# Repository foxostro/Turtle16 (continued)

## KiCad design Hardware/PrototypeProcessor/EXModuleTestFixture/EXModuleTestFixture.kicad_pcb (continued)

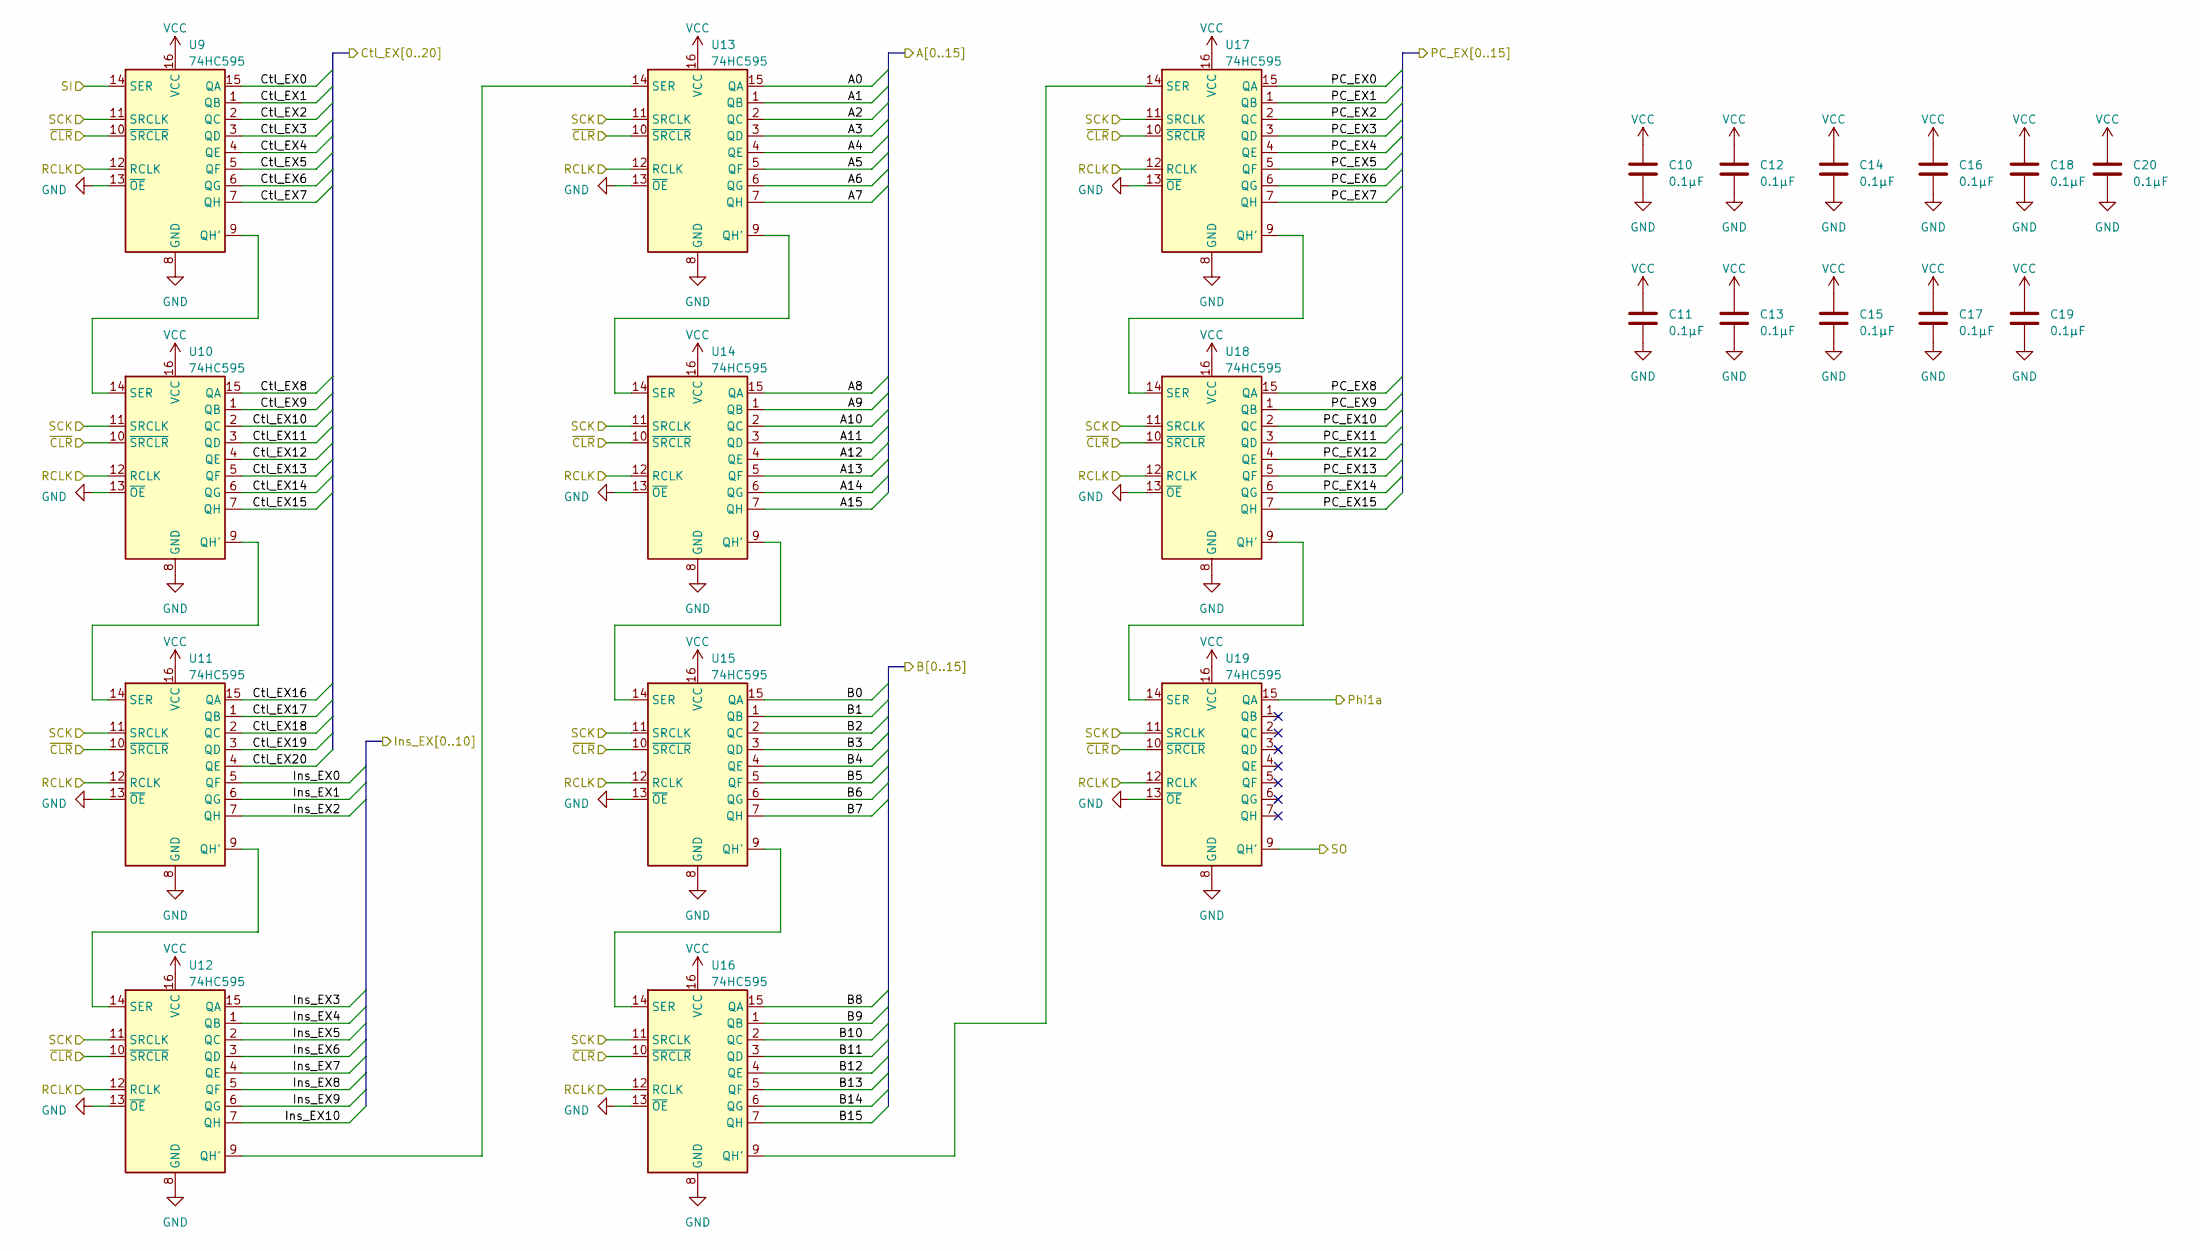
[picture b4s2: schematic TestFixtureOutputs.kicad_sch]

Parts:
C10, C11, C12, C13, C14, C15, C16, C17, C18, C19, C20: 0.1µF; C_0603_1608Metric
U9, U10, U11, U12, U13, U14, U15, U16, U17, U18, U19: 74HC595; TSSOP-16_4.4x5mm_P0.65mm

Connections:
/EX Prototype Inputs/A0: U13.15 (QA); also elsewhere on the board
/EX Prototype Inputs/A1: U13.1 (QB); also elsewhere on the board
/EX Prototype Inputs/A2: U13.2 (QC); also elsewhere on the board
/EX Prototype Inputs/A3: U13.3 (QD); also elsewhere on the board
/EX Prototype Inputs/A4: U13.4 (QE); also elsewhere on the board
/EX Prototype Inputs/A5: U13.5 (QF); also elsewhere on the board
/EX Prototype Inputs/A6: U13.6 (QG); also elsewhere on the board
/EX Prototype Inputs/A7: U13.7 (QH); also elsewhere on the board
/EX Prototype Inputs/A8: U14.15 (QA); also elsewhere on the board
/EX Prototype Inputs/A9: U14.1 (QB); also elsewhere on the board
/EX Prototype Inputs/A10: U14.2 (QC); also elsewhere on the board
/EX Prototype Inputs/A11: U14.3 (QD); also elsewhere on the board
/EX Prototype Inputs/A12: U14.4 (QE); also elsewhere on the board
/EX Prototype Inputs/A13: U14.5 (QF); also elsewhere on the board
/EX Prototype Inputs/A14: U14.6 (QG); also elsewhere on the board
/EX Prototype Inputs/A15: U14.7 (QH); also elsewhere on the board
/EX Prototype Inputs/B0: U15.15 (QA); also elsewhere on the board
/EX Prototype Inputs/B1: U15.1 (QB); also elsewhere on the board
/EX Prototype Inputs/B2: U15.2 (QC); also elsewhere on the board
/EX Prototype Inputs/B3: U15.3 (QD); also elsewhere on the board
/EX Prototype Inputs/B4: U15.4 (QE); also elsewhere on the board
/EX Prototype Inputs/B5: U15.5 (QF); also elsewhere on the board
/EX Prototype Inputs/B6: U15.6 (QG); also elsewhere on the board
/EX Prototype Inputs/B7: U15.7 (QH); also elsewhere on the board
/EX Prototype Inputs/B8: U16.15 (QA); also elsewhere on the board
/EX Prototype Inputs/B9: U16.1 (QB); also elsewhere on the board
/EX Prototype Inputs/B10: U16.2 (QC); also elsewhere on the board
/EX Prototype Inputs/B11: U16.3 (QD); also elsewhere on the board
/EX Prototype Inputs/B12: U16.4 (QE); also elsewhere on the board
/EX Prototype Inputs/B13: U16.5 (QF); also elsewhere on the board
/EX Prototype Inputs/B14: U16.6 (QG); also elsewhere on the board
/EX Prototype Inputs/B15: U16.7 (QH); also elsewhere on the board
/EX Prototype Inputs/Ctl_EX0: U9.15 (QA); also elsewhere on the board
/EX Prototype Inputs/Ctl_EX1: U9.1 (QB); also elsewhere on the board
/EX Prototype Inputs/Ctl_EX2: U9.2 (QC); also elsewhere on the board
/EX Prototype Inputs/Ctl_EX3: U9.3 (QD); also elsewhere on the board
/EX Prototype Inputs/Ctl_EX4: U9.4 (QE); also elsewhere on the board
/EX Prototype Inputs/Ctl_EX5: U9.5 (QF); also elsewhere on the board
/EX Prototype Inputs/Ctl_EX6: U9.6 (QG); also elsewhere on the board
/EX Prototype Inputs/Ctl_EX7: U9.7 (QH); also elsewhere on the board
/EX Prototype Inputs/Ctl_EX8: U10.15 (QA); also elsewhere on the board
/EX Prototype Inputs/Ctl_EX9: U10.1 (QB); also elsewhere on the board
/EX Prototype Inputs/Ctl_EX10: U10.2 (QC); also elsewhere on the board
/EX Prototype Inputs/Ctl_EX11: U10.3 (QD); also elsewhere on the board
/EX Prototype Inputs/Ctl_EX12: U10.4 (QE); also elsewhere on the board
/EX Prototype Inputs/Ctl_EX13: U10.5 (QF); also elsewhere on the board
/EX Prototype Inputs/Ctl_EX14: U10.6 (QG); also elsewhere on the board
/EX Prototype Inputs/Ctl_EX15: U10.7 (QH); also elsewhere on the board
/EX Prototype Inputs/Ctl_EX16: U11.15 (QA); also elsewhere on the board
/EX Prototype Inputs/Ctl_EX17: U11.1 (QB); also elsewhere on the board
/EX Prototype Inputs/Ctl_EX18: U11.2 (QC); also elsewhere on the board
/EX Prototype Inputs/Ctl_EX19: U11.3 (QD); also elsewhere on the board
/EX Prototype Inputs/Ctl_EX20: U11.4 (QE); also elsewhere on the board
/EX Prototype Inputs/Ins_EX0: U11.5 (QF); also elsewhere on the board
/EX Prototype Inputs/Ins_EX1: U11.6 (QG); also elsewhere on the board
/EX Prototype Inputs/Ins_EX2: U11.7 (QH); also elsewhere on the board
/EX Prototype Inputs/Ins_EX3: U12.15 (QA); also elsewhere on the board
/EX Prototype Inputs/Ins_EX4: U12.1 (QB); also elsewhere on the board
/EX Prototype Inputs/Ins_EX5: U12.2 (QC); also elsewhere on the board
/EX Prototype Inputs/Ins_EX6: U12.3 (QD); also elsewhere on the board
/EX Prototype Inputs/Ins_EX7: U12.4 (QE); also elsewhere on the board
/EX Prototype Inputs/Ins_EX8: U12.5 (QF); also elsewhere on the board
/EX Prototype Inputs/Ins_EX9: U12.6 (QG); also elsewhere on the board
/EX Prototype Inputs/Ins_EX10: U12.7 (QH); also elsewhere on the board
/EX Prototype Inputs/PC_EX0: U17.15 (QA); also elsewhere on the board
/EX Prototype Inputs/PC_EX1: U17.1 (QB); also elsewhere on the board
/EX Prototype Inputs/PC_EX2: U17.2 (QC); also elsewhere on the board
/EX Prototype Inputs/PC_EX3: U17.3 (QD); also elsewhere on the board
/EX Prototype Inputs/PC_EX4: U17.4 (QE); also elsewhere on the board
/EX Prototype Inputs/PC_EX5: U17.5 (QF); also elsewhere on the board
/EX Prototype Inputs/PC_EX6: U17.6 (QG); also elsewhere on the board
/EX Prototype Inputs/PC_EX7: U17.7 (QH); also elsewhere on the board
/EX Prototype Inputs/PC_EX8: U18.15 (QA); also elsewhere on the board
/EX Prototype Inputs/PC_EX9: U18.1 (QB); also elsewhere on the board
/EX Prototype Inputs/PC_EX10: U18.2 (QC); also elsewhere on the board
/EX Prototype Inputs/PC_EX11: U18.3 (QD); also elsewhere on the board
/EX Prototype Inputs/PC_EX12: U18.4 (QE); also elsewhere on the board
/EX Prototype Inputs/PC_EX13: U18.5 (QF); also elsewhere on the board
/EX Prototype Inputs/PC_EX14: U18.6 (QG); also elsewhere on the board
/EX Prototype Inputs/PC_EX15: U18.7 (QH); also elsewhere on the board
/EX Prototype Inputs/Phi1a: U19.15 (QA); also elsewhere on the board
/Test Fixture Outputs/RCLK: U9.12 (RCLK), U10.12 (RCLK), U11.12 (RCLK), U12.12 (RCLK), U13.12 (RCLK), U14.12 (RCLK), U15.12 (RCLK), U16.12 (RCLK), U17.12 (RCLK), U18.12 (RCLK), U19.12 (RCLK); also elsewhere on the board
/Test Fixture Outputs/SCK: U9.11 (SRCLK), U10.11 (SRCLK), U11.11 (SRCLK), U12.11 (SRCLK), U13.11 (SRCLK), U14.11 (SRCLK), U15.11 (SRCLK), U16.11 (SRCLK), U17.11 (SRCLK), U18.11 (SRCLK), U19.11 (SRCLK); also elsewhere on the board
/Test Fixture Outputs/SI: U9.14 (SER); also elsewhere on the board
/Test Fixture Outputs/SO: U19.9 (QH')
/Test Fixture Outputs/~CLR: U9.10 (~SRCLR), U10.10 (~SRCLR), U11.10 (~SRCLR), U12.10 (~SRCLR), U13.10 (~SRCLR), U14.10 (~SRCLR), U15.10 (~SRCLR), U16.10 (~SRCLR), U17.10 (~SRCLR), U18.10 (~SRCLR), U19.10 (~SRCLR); also elsewhere on the board
GND: C10.2, C11.2, C12.2, C13.2, C14.2, C15.2, C16.2, C17.2, C18.2, C19.2, C20.2, U9.8 (GND), U9.13 (~OE), U10.8 (GND), U10.13 (~OE), U11.8 (GND), U11.13 (~OE), U12.8 (GND), U12.13 (~OE), U13.8 (GND), U13.13 (~OE), U14.8 (GND), U14.13 (~OE), U15.8 (GND), U15.13 (~OE), U16.8 (GND), U16.13 (~OE), U17.8 (GND), U17.13 (~OE), U18.8 (GND), U18.13 (~OE), U19.8 (GND), U19.13 (~OE); also elsewhere on the board
unnamed: U10.9 (QH'), U11.14 (SER)
unnamed: U9.9 (QH'), U10.14 (SER)
unnamed: U11.9 (QH'), U12.14 (SER)
unnamed: U12.9 (QH'), U13.14 (SER)
unnamed: U13.9 (QH'), U14.14 (SER)
unnamed: U14.9 (QH'), U15.14 (SER)
unnamed: U15.9 (QH'), U16.14 (SER)
unnamed: U16.9 (QH'), U17.14 (SER)
unnamed: U17.9 (QH'), U18.14 (SER)
unnamed: U18.9 (QH'), U19.14 (SER)
VCC: C10.1, C11.1, C12.1, C13.1, C14.1, C15.1, C16.1, C17.1, C18.1, C19.1, C20.1, U9.16 (VCC), U10.16 (VCC), U11.16 (VCC), U12.16 (VCC), U13.16 (VCC), U14.16 (VCC), U15.16 (VCC), U16.16 (VCC), U17.16 (VCC), U18.16 (VCC), U19.16 (VCC); also elsewhere on the board

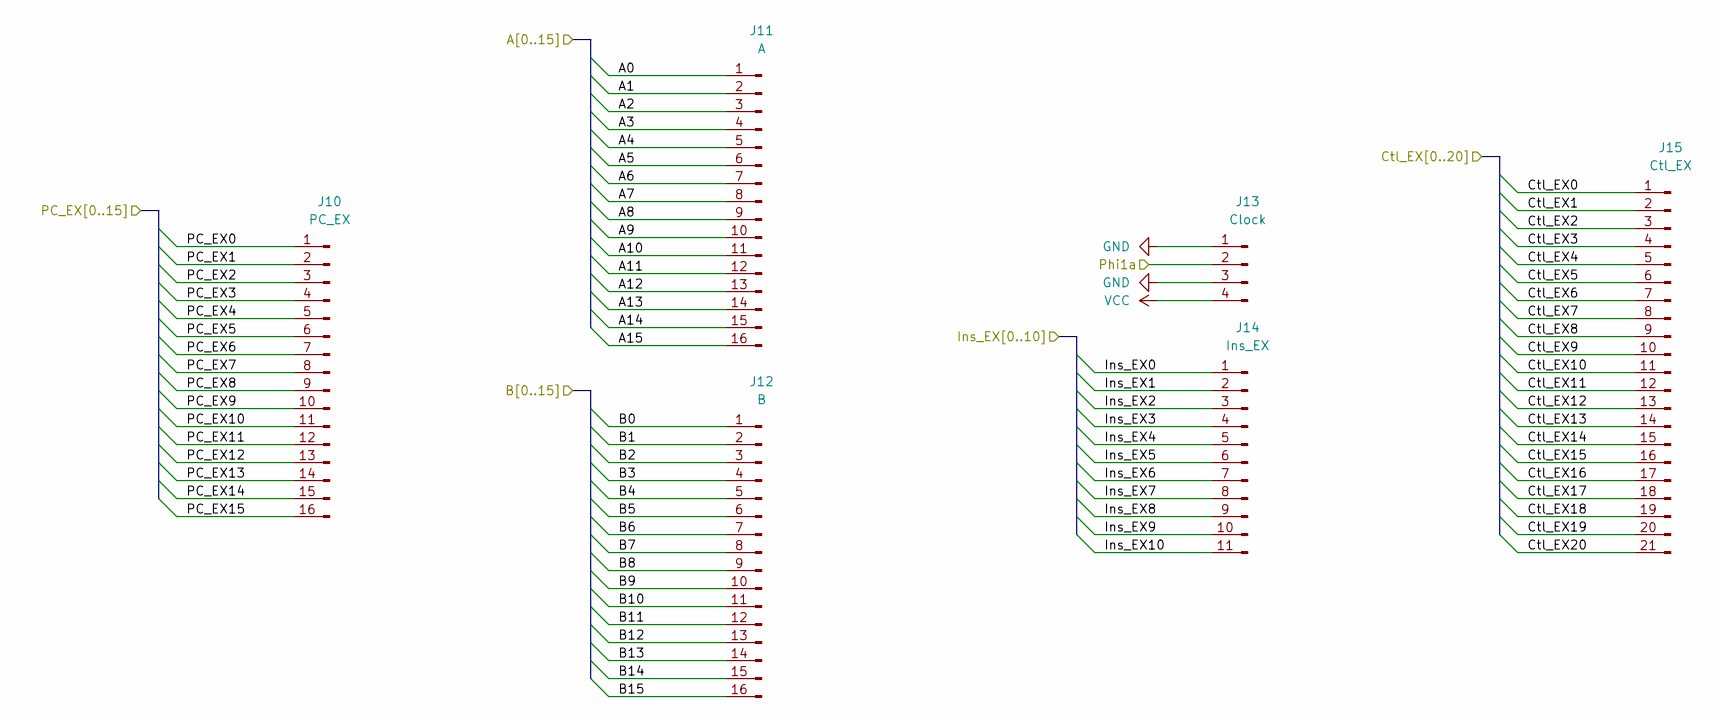
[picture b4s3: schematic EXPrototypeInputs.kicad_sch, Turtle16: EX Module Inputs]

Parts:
J10: PC_EX; PinHeader_1x16_P2.54mm_Vertical
J11: A; PinHeader_1x16_P2.54mm_Vertical
J12: B; PinHeader_1x16_P2.54mm_Vertical
J13: Clock; PinHeader_1x04_P2.54mm_Vertical
J14: Ins_EX; PinHeader_1x11_P2.54mm_Vertical
J15: Ctl_EX; PinHeader_1x21_P2.54mm_Vertical

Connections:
/EX Prototype Inputs/A0: J11.1; also elsewhere on the board
/EX Prototype Inputs/A1: J11.2; also elsewhere on the board
/EX Prototype Inputs/A2: J11.3; also elsewhere on the board
/EX Prototype Inputs/A3: J11.4; also elsewhere on the board
/EX Prototype Inputs/A4: J11.5; also elsewhere on the board
/EX Prototype Inputs/A5: J11.6; also elsewhere on the board
/EX Prototype Inputs/A6: J11.7; also elsewhere on the board
/EX Prototype Inputs/A7: J11.8; also elsewhere on the board
/EX Prototype Inputs/A8: J11.9; also elsewhere on the board
/EX Prototype Inputs/A9: J11.10; also elsewhere on the board
/EX Prototype Inputs/A10: J11.11; also elsewhere on the board
/EX Prototype Inputs/A11: J11.12; also elsewhere on the board
/EX Prototype Inputs/A12: J11.13; also elsewhere on the board
/EX Prototype Inputs/A13: J11.14; also elsewhere on the board
/EX Prototype Inputs/A14: J11.15; also elsewhere on the board
/EX Prototype Inputs/A15: J11.16; also elsewhere on the board
/EX Prototype Inputs/B0: J12.1; also elsewhere on the board
/EX Prototype Inputs/B1: J12.2; also elsewhere on the board
/EX Prototype Inputs/B2: J12.3; also elsewhere on the board
/EX Prototype Inputs/B3: J12.4; also elsewhere on the board
/EX Prototype Inputs/B4: J12.5; also elsewhere on the board
/EX Prototype Inputs/B5: J12.6; also elsewhere on the board
/EX Prototype Inputs/B6: J12.7; also elsewhere on the board
/EX Prototype Inputs/B7: J12.8; also elsewhere on the board
/EX Prototype Inputs/B8: J12.9; also elsewhere on the board
/EX Prototype Inputs/B9: J12.10; also elsewhere on the board
/EX Prototype Inputs/B10: J12.11; also elsewhere on the board
/EX Prototype Inputs/B11: J12.12; also elsewhere on the board
/EX Prototype Inputs/B12: J12.13; also elsewhere on the board
/EX Prototype Inputs/B13: J12.14; also elsewhere on the board
/EX Prototype Inputs/B14: J12.15; also elsewhere on the board
/EX Prototype Inputs/B15: J12.16; also elsewhere on the board
/EX Prototype Inputs/Ctl_EX0: J15.1; also elsewhere on the board
/EX Prototype Inputs/Ctl_EX1: J15.2; also elsewhere on the board
/EX Prototype Inputs/Ctl_EX2: J15.3; also elsewhere on the board
/EX Prototype Inputs/Ctl_EX3: J15.4; also elsewhere on the board
/EX Prototype Inputs/Ctl_EX4: J15.5; also elsewhere on the board
/EX Prototype Inputs/Ctl_EX5: J15.6; also elsewhere on the board
/EX Prototype Inputs/Ctl_EX6: J15.7; also elsewhere on the board
/EX Prototype Inputs/Ctl_EX7: J15.8; also elsewhere on the board
/EX Prototype Inputs/Ctl_EX8: J15.9; also elsewhere on the board
/EX Prototype Inputs/Ctl_EX9: J15.10; also elsewhere on the board
/EX Prototype Inputs/Ctl_EX10: J15.11; also elsewhere on the board
/EX Prototype Inputs/Ctl_EX11: J15.12; also elsewhere on the board
/EX Prototype Inputs/Ctl_EX12: J15.13; also elsewhere on the board
/EX Prototype Inputs/Ctl_EX13: J15.14; also elsewhere on the board
/EX Prototype Inputs/Ctl_EX14: J15.15; also elsewhere on the board
/EX Prototype Inputs/Ctl_EX15: J15.16; also elsewhere on the board
/EX Prototype Inputs/Ctl_EX16: J15.17; also elsewhere on the board
/EX Prototype Inputs/Ctl_EX17: J15.18; also elsewhere on the board
/EX Prototype Inputs/Ctl_EX18: J15.19; also elsewhere on the board
/EX Prototype Inputs/Ctl_EX19: J15.20; also elsewhere on the board
/EX Prototype Inputs/Ctl_EX20: J15.21; also elsewhere on the board
/EX Prototype Inputs/Ins_EX0: J14.1; also elsewhere on the board
/EX Prototype Inputs/Ins_EX1: J14.2; also elsewhere on the board
/EX Prototype Inputs/Ins_EX2: J14.3; also elsewhere on the board
/EX Prototype Inputs/Ins_EX3: J14.4; also elsewhere on the board
/EX Prototype Inputs/Ins_EX4: J14.5; also elsewhere on the board
/EX Prototype Inputs/Ins_EX5: J14.6; also elsewhere on the board
/EX Prototype Inputs/Ins_EX6: J14.7; also elsewhere on the board
/EX Prototype Inputs/Ins_EX7: J14.8; also elsewhere on the board
/EX Prototype Inputs/Ins_EX8: J14.9; also elsewhere on the board
/EX Prototype Inputs/Ins_EX9: J14.10; also elsewhere on the board
/EX Prototype Inputs/Ins_EX10: J14.11; also elsewhere on the board
/EX Prototype Inputs/PC_EX0: J10.1; also elsewhere on the board
/EX Prototype Inputs/PC_EX1: J10.2; also elsewhere on the board
/EX Prototype Inputs/PC_EX2: J10.3; also elsewhere on the board
/EX Prototype Inputs/PC_EX3: J10.4; also elsewhere on the board
/EX Prototype Inputs/PC_EX4: J10.5; also elsewhere on the board
/EX Prototype Inputs/PC_EX5: J10.6; also elsewhere on the board
/EX Prototype Inputs/PC_EX6: J10.7; also elsewhere on the board
/EX Prototype Inputs/PC_EX7: J10.8; also elsewhere on the board
/EX Prototype Inputs/PC_EX8: J10.9; also elsewhere on the board
/EX Prototype Inputs/PC_EX9: J10.10; also elsewhere on the board
/EX Prototype Inputs/PC_EX10: J10.11; also elsewhere on the board
/EX Prototype Inputs/PC_EX11: J10.12; also elsewhere on the board
/EX Prototype Inputs/PC_EX12: J10.13; also elsewhere on the board
/EX Prototype Inputs/PC_EX13: J10.14; also elsewhere on the board
/EX Prototype Inputs/PC_EX14: J10.15; also elsewhere on the board
/EX Prototype Inputs/PC_EX15: J10.16; also elsewhere on the board
/EX Prototype Inputs/Phi1a: J13.2; also elsewhere on the board
GND: J13.1, J13.3; also elsewhere on the board
VCC: J13.4; also elsewhere on the board

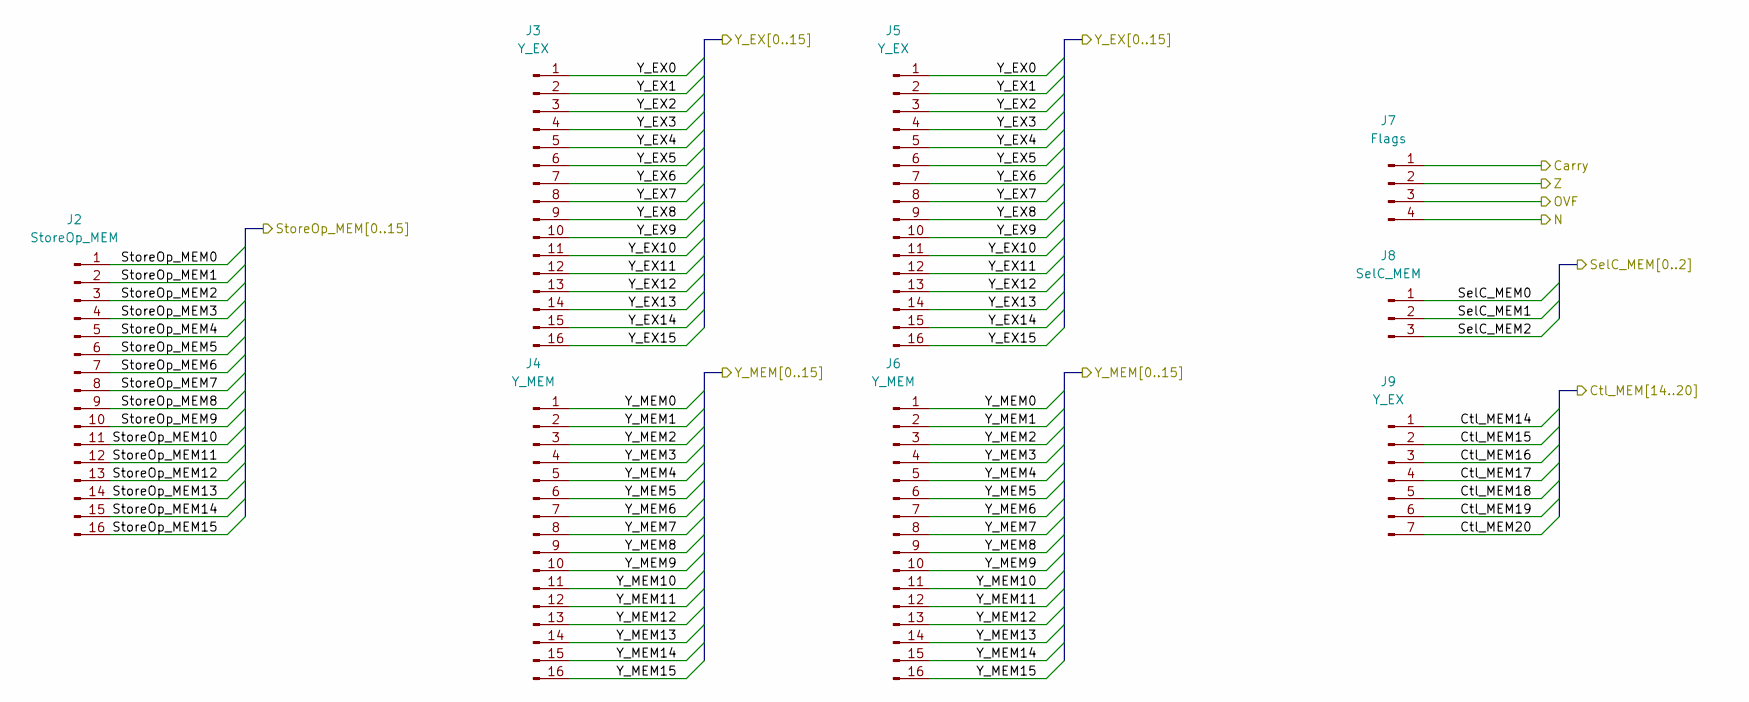
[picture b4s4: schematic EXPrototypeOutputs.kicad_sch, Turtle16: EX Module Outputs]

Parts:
J2: StoreOp_MEM; PinHeader_1x16_P2.54mm_Vertical
J3, J5: Y_EX; PinHeader_1x16_P2.54mm_Vertical
J4, J6: Y_MEM; PinHeader_1x16_P2.54mm_Vertical
J7: Flags; PinHeader_1x04_P2.54mm_Vertical
J8: SelC_MEM; PinHeader_1x03_P2.54mm_Vertical
J9: Y_EX; PinHeader_1x07_P2.54mm_Vertical

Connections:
/EX Prototype Outputs/Carry: J7.1; also elsewhere on the board
/EX Prototype Outputs/Ctl_MEM14: J9.1; also elsewhere on the board
/EX Prototype Outputs/Ctl_MEM15: J9.2; also elsewhere on the board
/EX Prototype Outputs/Ctl_MEM16: J9.3; also elsewhere on the board
/EX Prototype Outputs/Ctl_MEM17: J9.4; also elsewhere on the board
/EX Prototype Outputs/Ctl_MEM18: J9.5; also elsewhere on the board
/EX Prototype Outputs/Ctl_MEM19: J9.6; also elsewhere on the board
/EX Prototype Outputs/Ctl_MEM20: J9.7; also elsewhere on the board
/EX Prototype Outputs/N: J7.4; also elsewhere on the board
/EX Prototype Outputs/OVF: J7.3; also elsewhere on the board
/EX Prototype Outputs/SelC_MEM0: J8.1; also elsewhere on the board
/EX Prototype Outputs/SelC_MEM1: J8.2; also elsewhere on the board
/EX Prototype Outputs/SelC_MEM2: J8.3; also elsewhere on the board
/EX Prototype Outputs/StoreOp_MEM0: J2.1; also elsewhere on the board
/EX Prototype Outputs/StoreOp_MEM1: J2.2; also elsewhere on the board
/EX Prototype Outputs/StoreOp_MEM2: J2.3; also elsewhere on the board
/EX Prototype Outputs/StoreOp_MEM3: J2.4; also elsewhere on the board
/EX Prototype Outputs/StoreOp_MEM4: J2.5; also elsewhere on the board
/EX Prototype Outputs/StoreOp_MEM5: J2.6; also elsewhere on the board
/EX Prototype Outputs/StoreOp_MEM6: J2.7; also elsewhere on the board
/EX Prototype Outputs/StoreOp_MEM7: J2.8; also elsewhere on the board
/EX Prototype Outputs/StoreOp_MEM8: J2.9; also elsewhere on the board
/EX Prototype Outputs/StoreOp_MEM9: J2.10; also elsewhere on the board
/EX Prototype Outputs/StoreOp_MEM10: J2.11; also elsewhere on the board
/EX Prototype Outputs/StoreOp_MEM11: J2.12; also elsewhere on the board
/EX Prototype Outputs/StoreOp_MEM12: J2.13; also elsewhere on the board
/EX Prototype Outputs/StoreOp_MEM13: J2.14; also elsewhere on the board
/EX Prototype Outputs/StoreOp_MEM14: J2.15; also elsewhere on the board
/EX Prototype Outputs/StoreOp_MEM15: J2.16; also elsewhere on the board
/EX Prototype Outputs/Y_EX0: J3.1, J5.1; also elsewhere on the board
/EX Prototype Outputs/Y_EX1: J3.2, J5.2; also elsewhere on the board
/EX Prototype Outputs/Y_EX2: J3.3, J5.3; also elsewhere on the board
/EX Prototype Outputs/Y_EX3: J3.4, J5.4; also elsewhere on the board
/EX Prototype Outputs/Y_EX4: J3.5, J5.5; also elsewhere on the board
/EX Prototype Outputs/Y_EX5: J3.6, J5.6; also elsewhere on the board
/EX Prototype Outputs/Y_EX6: J3.7, J5.7; also elsewhere on the board
/EX Prototype Outputs/Y_EX7: J3.8, J5.8; also elsewhere on the board
/EX Prototype Outputs/Y_EX8: J3.9, J5.9; also elsewhere on the board
/EX Prototype Outputs/Y_EX9: J3.10, J5.10; also elsewhere on the board
/EX Prototype Outputs/Y_EX10: J3.11, J5.11; also elsewhere on the board
/EX Prototype Outputs/Y_EX11: J3.12, J5.12; also elsewhere on the board
/EX Prototype Outputs/Y_EX12: J3.13, J5.13; also elsewhere on the board
/EX Prototype Outputs/Y_EX13: J3.14, J5.14; also elsewhere on the board
/EX Prototype Outputs/Y_EX14: J3.15, J5.15; also elsewhere on the board
/EX Prototype Outputs/Y_EX15: J3.16, J5.16; also elsewhere on the board
/EX Prototype Outputs/Y_MEM0: J4.1, J6.1; also elsewhere on the board
/EX Prototype Outputs/Y_MEM1: J4.2, J6.2; also elsewhere on the board
/EX Prototype Outputs/Y_MEM2: J4.3, J6.3; also elsewhere on the board
/EX Prototype Outputs/Y_MEM3: J4.4, J6.4; also elsewhere on the board
/EX Prototype Outputs/Y_MEM4: J4.5, J6.5; also elsewhere on the board
/EX Prototype Outputs/Y_MEM5: J4.6, J6.6; also elsewhere on the board
/EX Prototype Outputs/Y_MEM6: J4.7, J6.7; also elsewhere on the board
/EX Prototype Outputs/Y_MEM7: J4.8, J6.8; also elsewhere on the board
/EX Prototype Outputs/Y_MEM8: J4.9, J6.9; also elsewhere on the board
/EX Prototype Outputs/Y_MEM9: J4.10, J6.10; also elsewhere on the board
/EX Prototype Outputs/Y_MEM10: J4.11, J6.11; also elsewhere on the board
/EX Prototype Outputs/Y_MEM11: J4.12, J6.12; also elsewhere on the board
/EX Prototype Outputs/Y_MEM12: J4.13, J6.13; also elsewhere on the board
/EX Prototype Outputs/Y_MEM13: J4.14, J6.14; also elsewhere on the board
/EX Prototype Outputs/Y_MEM14: J4.15, J6.15; also elsewhere on the board
/EX Prototype Outputs/Y_MEM15: J4.16, J6.16; also elsewhere on the board
/EX Prototype Outputs/Z: J7.2; also elsewhere on the board

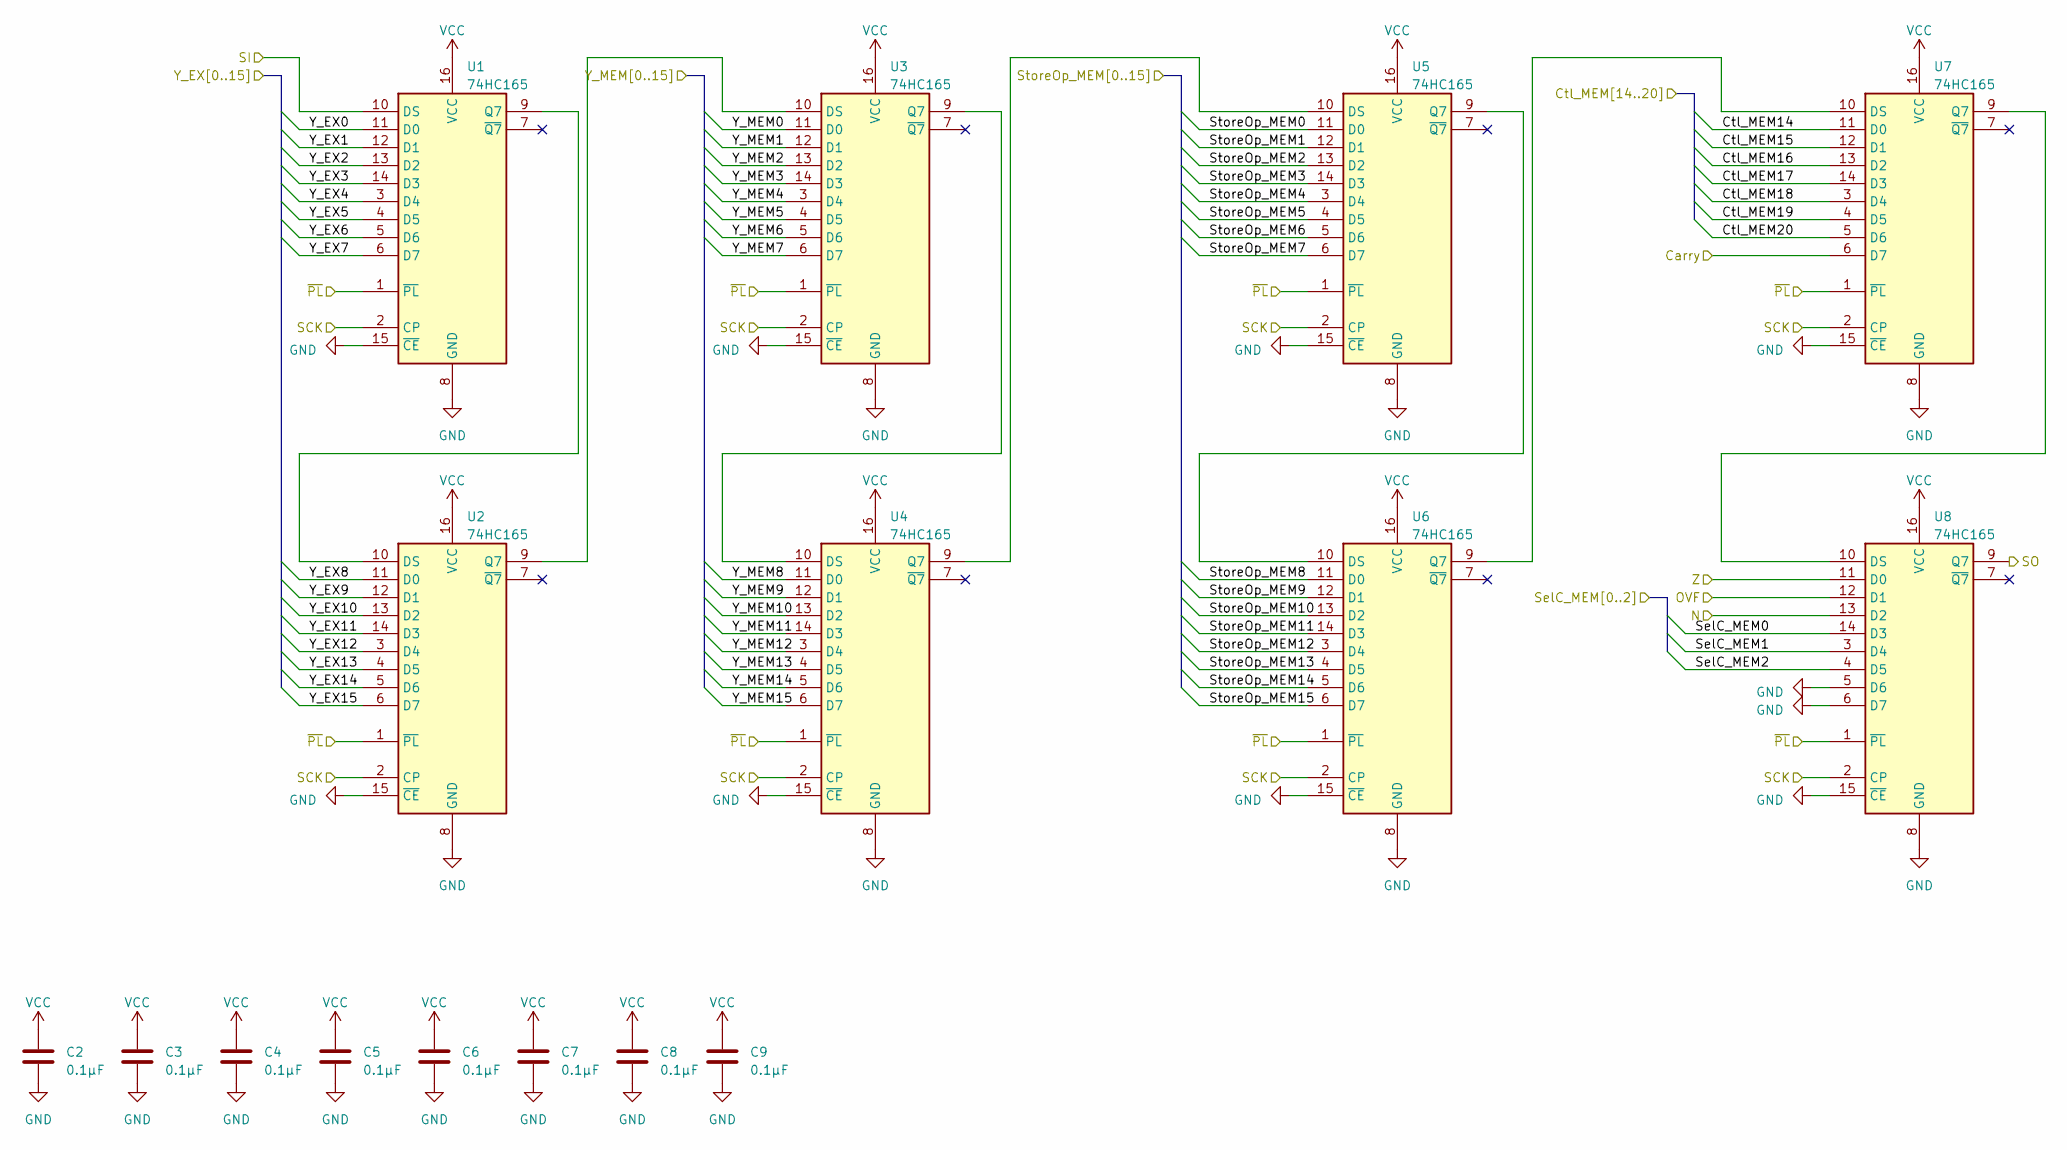
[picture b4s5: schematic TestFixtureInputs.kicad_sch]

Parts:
C2, C3, C4, C5, C6, C7, C8, C9: 0.1µF; C_0603_1608Metric
U1, U2, U3, U4, U5, U6, U7, U8: 74HC165; TSSOP-16_4.4x5mm_P0.65mm

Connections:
/EX Prototype Outputs/Carry: U7.6 (D7); also elsewhere on the board
/EX Prototype Outputs/Ctl_MEM14: U7.11 (D0); also elsewhere on the board
/EX Prototype Outputs/Ctl_MEM15: U7.12 (D1); also elsewhere on the board
/EX Prototype Outputs/Ctl_MEM16: U7.13 (D2); also elsewhere on the board
/EX Prototype Outputs/Ctl_MEM17: U7.14 (D3); also elsewhere on the board
/EX Prototype Outputs/Ctl_MEM18: U7.3 (D4); also elsewhere on the board
/EX Prototype Outputs/Ctl_MEM19: U7.4 (D5); also elsewhere on the board
/EX Prototype Outputs/Ctl_MEM20: U7.5 (D6); also elsewhere on the board
/EX Prototype Outputs/N: U8.13 (D2); also elsewhere on the board
/EX Prototype Outputs/OVF: U8.12 (D1); also elsewhere on the board
/EX Prototype Outputs/SelC_MEM0: U8.14 (D3); also elsewhere on the board
/EX Prototype Outputs/SelC_MEM1: U8.3 (D4); also elsewhere on the board
/EX Prototype Outputs/SelC_MEM2: U8.4 (D5); also elsewhere on the board
/EX Prototype Outputs/StoreOp_MEM0: U5.11 (D0); also elsewhere on the board
/EX Prototype Outputs/StoreOp_MEM1: U5.12 (D1); also elsewhere on the board
/EX Prototype Outputs/StoreOp_MEM2: U5.13 (D2); also elsewhere on the board
/EX Prototype Outputs/StoreOp_MEM3: U5.14 (D3); also elsewhere on the board
/EX Prototype Outputs/StoreOp_MEM4: U5.3 (D4); also elsewhere on the board
/EX Prototype Outputs/StoreOp_MEM5: U5.4 (D5); also elsewhere on the board
/EX Prototype Outputs/StoreOp_MEM6: U5.5 (D6); also elsewhere on the board
/EX Prototype Outputs/StoreOp_MEM7: U5.6 (D7); also elsewhere on the board
/EX Prototype Outputs/StoreOp_MEM8: U6.11 (D0); also elsewhere on the board
/EX Prototype Outputs/StoreOp_MEM9: U6.12 (D1); also elsewhere on the board
/EX Prototype Outputs/StoreOp_MEM10: U6.13 (D2); also elsewhere on the board
/EX Prototype Outputs/StoreOp_MEM11: U6.14 (D3); also elsewhere on the board
/EX Prototype Outputs/StoreOp_MEM12: U6.3 (D4); also elsewhere on the board
/EX Prototype Outputs/StoreOp_MEM13: U6.4 (D5); also elsewhere on the board
/EX Prototype Outputs/StoreOp_MEM14: U6.5 (D6); also elsewhere on the board
/EX Prototype Outputs/StoreOp_MEM15: U6.6 (D7); also elsewhere on the board
/EX Prototype Outputs/Y_EX0: U1.11 (D0); also elsewhere on the board
/EX Prototype Outputs/Y_EX1: U1.12 (D1); also elsewhere on the board
/EX Prototype Outputs/Y_EX2: U1.13 (D2); also elsewhere on the board
/EX Prototype Outputs/Y_EX3: U1.14 (D3); also elsewhere on the board
/EX Prototype Outputs/Y_EX4: U1.3 (D4); also elsewhere on the board
/EX Prototype Outputs/Y_EX5: U1.4 (D5); also elsewhere on the board
/EX Prototype Outputs/Y_EX6: U1.5 (D6); also elsewhere on the board
/EX Prototype Outputs/Y_EX7: U1.6 (D7); also elsewhere on the board
/EX Prototype Outputs/Y_EX8: U2.11 (D0); also elsewhere on the board
/EX Prototype Outputs/Y_EX9: U2.12 (D1); also elsewhere on the board
/EX Prototype Outputs/Y_EX10: U2.13 (D2); also elsewhere on the board
/EX Prototype Outputs/Y_EX11: U2.14 (D3); also elsewhere on the board
/EX Prototype Outputs/Y_EX12: U2.3 (D4); also elsewhere on the board
/EX Prototype Outputs/Y_EX13: U2.4 (D5); also elsewhere on the board
/EX Prototype Outputs/Y_EX14: U2.5 (D6); also elsewhere on the board
/EX Prototype Outputs/Y_EX15: U2.6 (D7); also elsewhere on the board
/EX Prototype Outputs/Y_MEM0: U3.11 (D0); also elsewhere on the board
/EX Prototype Outputs/Y_MEM1: U3.12 (D1); also elsewhere on the board
/EX Prototype Outputs/Y_MEM2: U3.13 (D2); also elsewhere on the board
/EX Prototype Outputs/Y_MEM3: U3.14 (D3); also elsewhere on the board
/EX Prototype Outputs/Y_MEM4: U3.3 (D4); also elsewhere on the board
/EX Prototype Outputs/Y_MEM5: U3.4 (D5); also elsewhere on the board
/EX Prototype Outputs/Y_MEM6: U3.5 (D6); also elsewhere on the board
/EX Prototype Outputs/Y_MEM7: U3.6 (D7); also elsewhere on the board
/EX Prototype Outputs/Y_MEM8: U4.11 (D0); also elsewhere on the board
/EX Prototype Outputs/Y_MEM9: U4.12 (D1); also elsewhere on the board
/EX Prototype Outputs/Y_MEM10: U4.13 (D2); also elsewhere on the board
/EX Prototype Outputs/Y_MEM11: U4.14 (D3); also elsewhere on the board
/EX Prototype Outputs/Y_MEM12: U4.3 (D4); also elsewhere on the board
/EX Prototype Outputs/Y_MEM13: U4.4 (D5); also elsewhere on the board
/EX Prototype Outputs/Y_MEM14: U4.5 (D6); also elsewhere on the board
/EX Prototype Outputs/Y_MEM15: U4.6 (D7); also elsewhere on the board
/EX Prototype Outputs/Z: U8.11 (D0); also elsewhere on the board
/Test Fixture Inputs/SCK: U1.2 (CP), U2.2 (CP), U3.2 (CP), U4.2 (CP), U5.2 (CP), U6.2 (CP), U7.2 (CP), U8.2 (CP); also elsewhere on the board
/Test Fixture Inputs/SO: U8.9 (Q7); also elsewhere on the board
/Test Fixture Inputs/~PL: U1.1 (~PL), U2.1 (~PL), U3.1 (~PL), U4.1 (~PL), U5.1 (~PL), U6.1 (~PL), U7.1 (~PL), U8.1 (~PL); also elsewhere on the board
GND: C2.2, C3.2, C4.2, C5.2, C6.2, C7.2, C8.2, C9.2, U1.8 (GND), U1.10 (DS), U1.15 (~CE), U2.8 (GND), U2.15 (~CE), U3.8 (GND), U3.15 (~CE), U4.8 (GND), U4.15 (~CE), U5.8 (GND), U5.15 (~CE), U6.8 (GND), U6.15 (~CE), U7.8 (GND), U7.15 (~CE), U8.5 (D6), U8.6 (D7), U8.8 (GND), U8.15 (~CE); also elsewhere on the board
unnamed: U1.9 (Q7), U2.10 (DS)
unnamed: U2.9 (Q7), U3.10 (DS)
unnamed: U3.9 (Q7), U4.10 (DS)
unnamed: U4.9 (Q7), U5.10 (DS)
unnamed: U5.9 (Q7), U6.10 (DS)
unnamed: U6.9 (Q7), U7.10 (DS)
unnamed: U7.9 (Q7), U8.10 (DS)
VCC: C2.1, C3.1, C4.1, C5.1, C6.1, C7.1, C8.1, C9.1, U1.16 (VCC), U2.16 (VCC), U3.16 (VCC), U4.16 (VCC), U5.16 (VCC), U6.16 (VCC), U7.16 (VCC), U8.16 (VCC); also elsewhere on the board
